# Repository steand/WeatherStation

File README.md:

# Wetterstation

Version 0.1 *(under construction, not stabil)*

In diesem Projekt habe ich mir eine kleine Wetterstation gebaut.
Meine Motivation war, dass es eigentlich nichts erschwingliches gibt was in die offenen Smart-Home (bei mir openHAB2) integrierbar ist.

Leistungsmerkmale:
- Windgeschwindigkeit
- Windrichtung
- Regenmenge
- Regensensor
- Temperatur
- Luftdruck
- Luftfeuchtigkeit
- Helligkeit

Zur Steuerung meine Markise benötige ich Alarme für Regen und Windgeschwindigkeit.
Die Rolladen werden mit Hilfe der Helligkeitssensor gesteuert.

Für Windgeschwindigkeit, -richtung und Regenmenge dienen die Sensoren eine AOK5055.
Regensensor ist ein "China Modul".
Temperatur, Luftdruck und -feuchte basieren auf einem BME280,
Helligkeit auf dem BH1750.

Die Microcontroller Basis ist  ESP-WROOM-32u (u wegen der Antenne).

Als Stromversorung dient eine 18500/3000mAh Batterie die über ein Modul(TP4056) geladen wird.
Der Lader wird über ein MPPT-Modul (China) von einem 5W/12V Solarpenel versorgt.
Als SDK setze ich platformIO auf Basis von Atom ein.
Für Schaltpläne und Platinenlayout (Entwicklerplatine) nutze ich KiCad.

Weitere Details unter dem Verzeichnis ```
./doc
```.

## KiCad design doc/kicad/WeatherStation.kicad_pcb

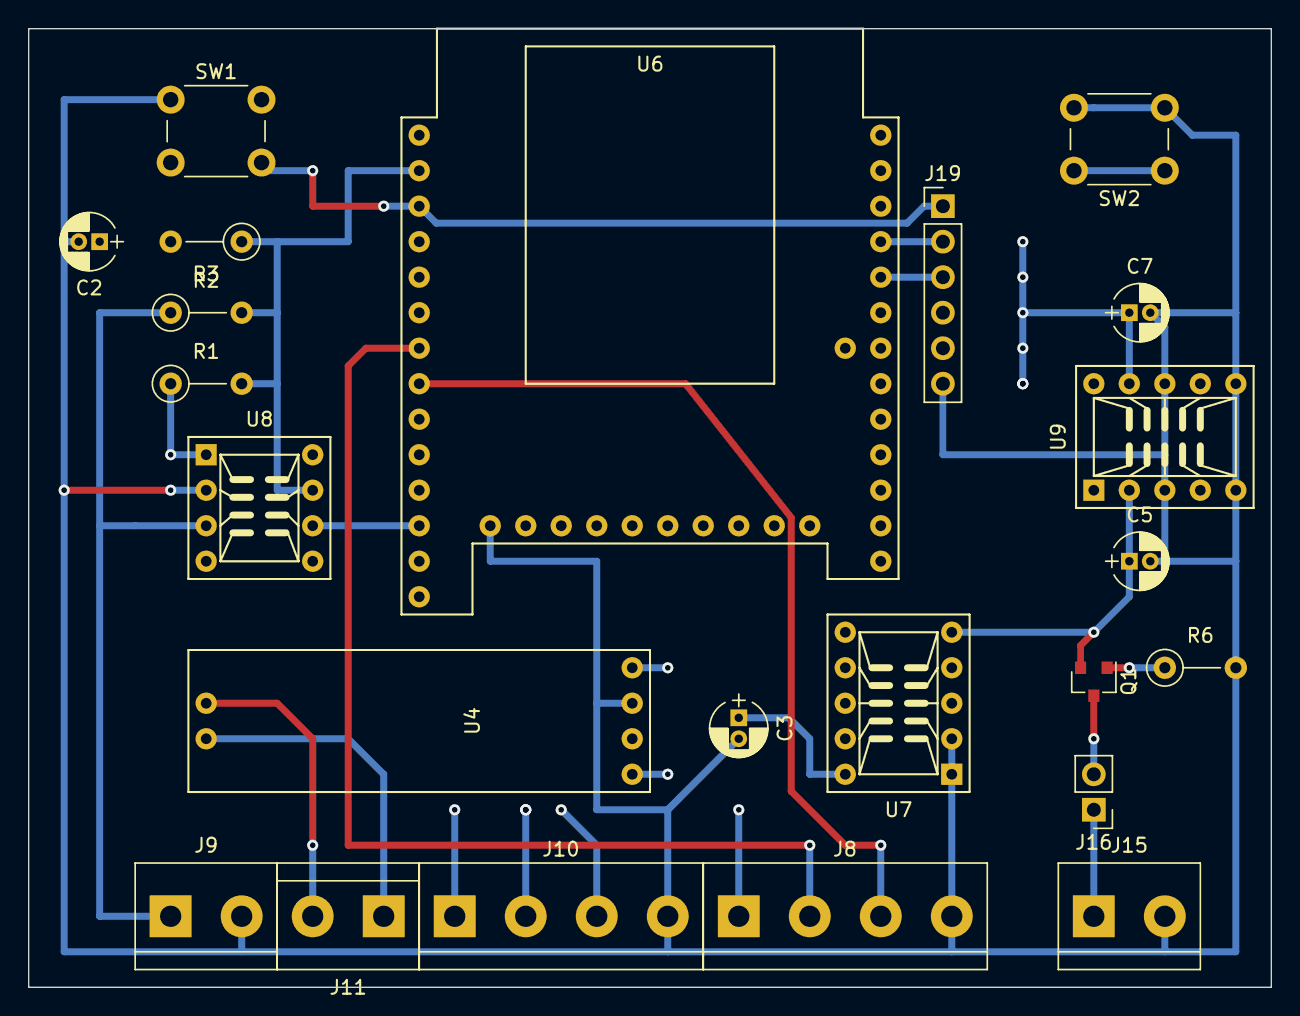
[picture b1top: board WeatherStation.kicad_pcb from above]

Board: 4 copper layers, 88.9 x 68.6 mm, 23 parts (0 on the bottom side), 23 nets.

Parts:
C2: 1µF; CP_Radial_D4.0mm_P1.50mm
C3, C7: 10µ; CP_Radial_D4.0mm_P1.50mm
C5: 1µ; CP_Radial_D4.0mm_P1.50mm
J8, J10: Screw_Terminal_01x04; TerminalBlock_bornier-4_P5.08mm
J9, J11, J15: Screw_Terminal_01x02; TerminalBlock_bornier-2_P5.08mm
J16: Conn_01x02_Male; Pin_Header_Straight_1x02_Pitch2.54mm
J19: Prog; Socket_Strip_Straight_1x06_Pitch2.54mm
Q1: IRLML2244; SOT-23
R1, R2: 100k; R_Axial_DIN0207_L6.3mm_D2.5mm_P5.08mm_Vertical
R3, R6: 10K; R_Axial_DIN0207_L6.3mm_D2.5mm_P5.08mm_Vertical
SW1: Reset; SW_PUSH_6mm
SW2: Mode; SW_PUSH_6mm
U4: Rain_Sensor
U6: ESP-WROOM-32; ESP32_Dev_Board
U7: Mod_Spannungsteiler; Mod_SOT23_TO_10DIL
U8: Mod_Dual_Schmitt_Triger; Mod_TSOP6_TO_8DIL
U9: Mod_Regulator_3.0V; Mod_SOT23_TO_10DIL

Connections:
+3V0: C7.1, J8.1, R1.2, R2.2, R3.1, U6.2, U7.4, U8.7, U9.9
+BATT: C5.1, Q1.2, U7.5, U9.2
/ADC1: C3.1, U6.4, U7.10
/ADC2: U4.4, U6.5
/DATA: J10.2, U6.10
/INT: U6.11, U8.8
/INT\EXT0: U6.12, U8.6
/PROG: J19.5, SW2.1, U6.25
/Power1: U4.1, U6.6
/Power2: J10.1, U6.9
/RST: C2.1, J19.1, R3.2, SW1.2, U6.3
/RxD: J19.3, U6.34
/SDA: J8.3, U6.8
/SLC: J8.2, U6.7
/TxD: J19.2, U6.35
/WindTic: J10.3, R1.1, U8.1
GND: C2.2, C3.2, C5.2, C7.2, J8.4, J9.2, J10.4, J15.2, J19.6, R6.2, SW1.1, SW2.2, U4.3, U6.15, U7.1, U7.2, U8.2, U9.3
unnamed: J9.1, R2.1, U8.3
unnamed: J11.1, U4.6
unnamed: J11.2, U4.5
unnamed: J15.1, J16.1
unnamed: J16.2, Q1.3
unnamed: Q1.1, R6.1

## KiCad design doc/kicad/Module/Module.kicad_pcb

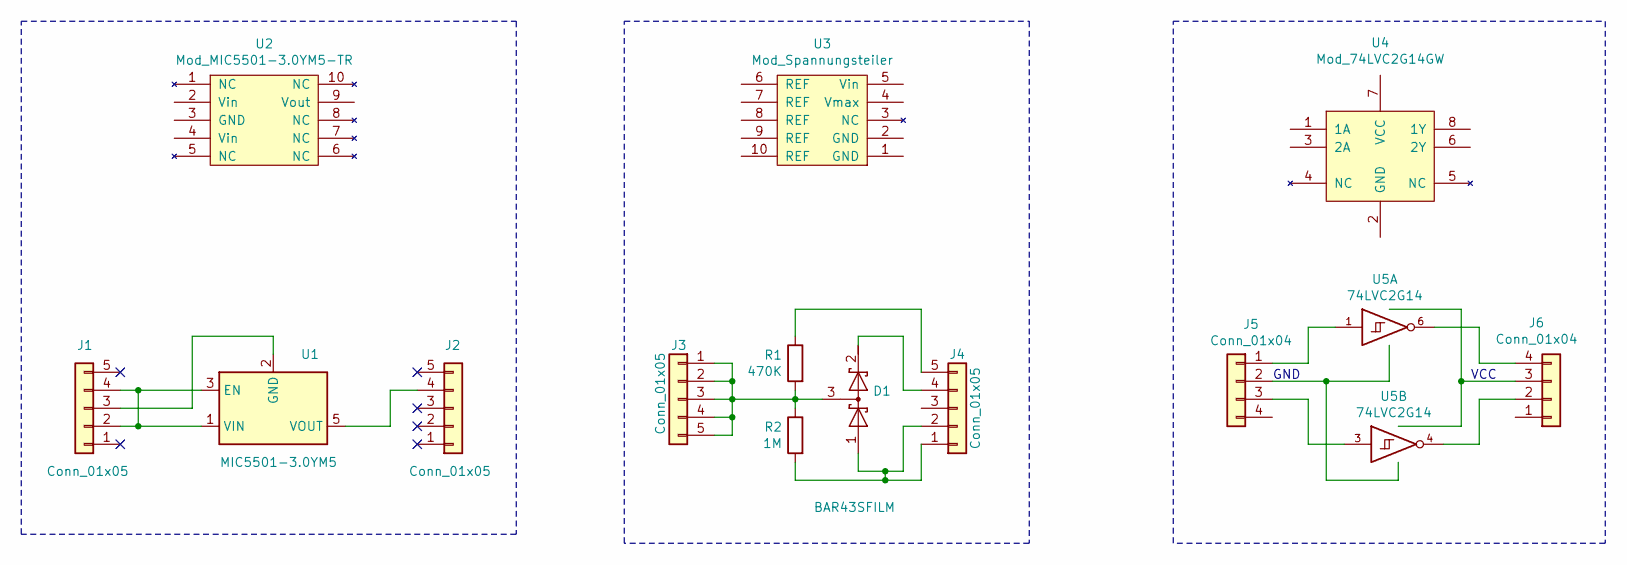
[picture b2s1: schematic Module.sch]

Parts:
D1: BAR43SFILM; SOT-23
J1, J2: Conn_01x05; Pin_Header_Straight_1x05_Pitch2.54mm
J3, J4: Conn_01x05; Socket_Strip_Straight_1x05_Pitch2.54mm
J5, J6: Conn_01x04; Socket_Strip_Straight_1x04_Pitch2.54mm
R1: 470K; R_0805
R2: 1M; R_0805
U1: MIC5501-3.0YM5; SOT-23-5
U2: Mod_MIC5501-3.0YM5-TR; Mod_SOT23_TO_10DIL
U3: Mod_Spannungsteiler; Mod_SOT23_TO_10DIL
U4: Mod_74LVC2G14GW; Mod_TSOP6_TO_8DIL
U5: 74LVC2G14; SOT-363_SC-70-6

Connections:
GND: J5.2, U5.2 (GND)
unnamed: D1.1 (A), J4.1, J4.2, R2.2
unnamed: D1.2 (K), J4.4
unnamed: D1.3 (AK), J3.1, J3.2, J3.3, J3.4, J3.5, R1.2, R2.1
unnamed: J1.2, J1.4, U1.1 (VIN), U1.3 (EN)
unnamed: J1.3, U1.2 (GND)
unnamed: J2.4, U1.5 (VOUT)
unnamed: J4.5, R1.1
unnamed: J5.1, U5.1
unnamed: J5.3, U5.3
unnamed: J6.2, U5.4
unnamed: J6.4, U5.6
VCC: J6.3, U5.5 (VCC)

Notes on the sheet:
VCC
GND

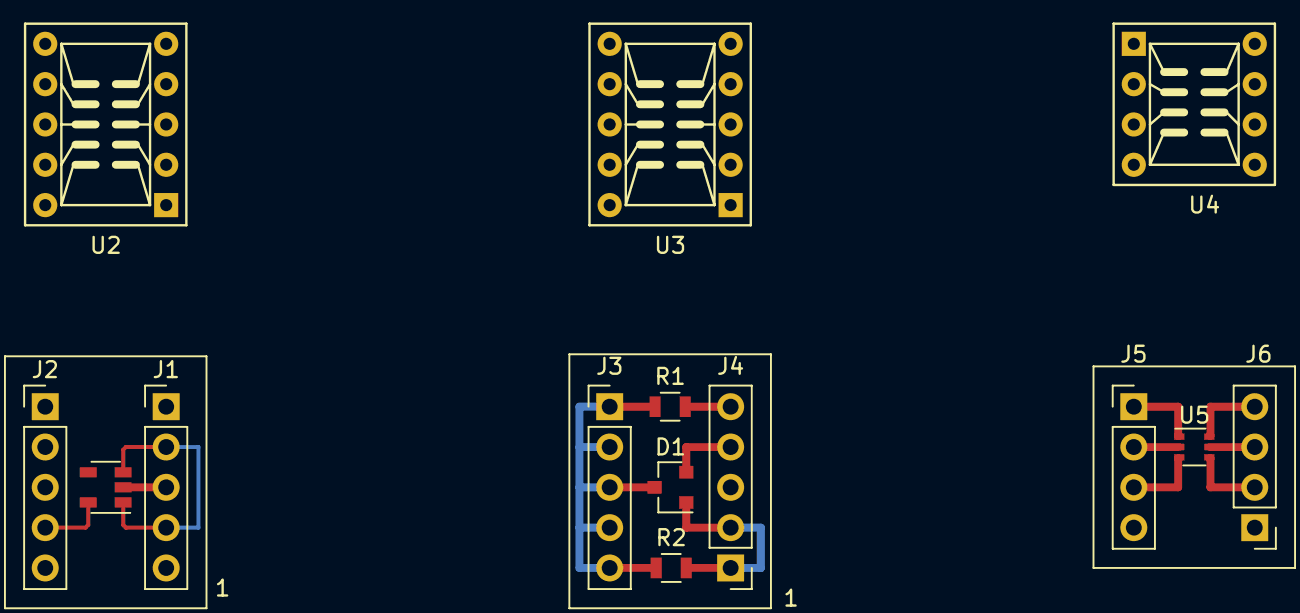
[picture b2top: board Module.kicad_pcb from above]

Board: 2 copper layers, 14 parts (0 on the bottom side), 13 nets.

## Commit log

2019-08-20 V0.1 (first Version)
2019-08-21 GPL Comments
2019-08-31 Stable without Solar monitor
2019-08-31 Stable bevor optimice loops
2019-09-13 Fixed WiFi freeze (ADC_2/Int Problems). Optimize Solar MPPT.
